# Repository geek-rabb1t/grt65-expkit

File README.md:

# GR-Trackpad65 experiment kit

The GR-Trackpad65 Experimental Kit is a kit for trying out the [GR-Trackpad65](https://github.com/geek-rabb1t/GR-Trackpad65).

It works as a macro pad with a trackpad for multi-touch support up to 4 fingers.

## Directory structure

This repository contains hardware design data only.

- pcb
    - PCB data designed by KiCAD.

## About Firmware

Vial firmware can be obtained from the following URL

- Vial
    - https://github.com/geek-rabb1t/vial-qmk/tree/gr_master/keyboards/geek_rabb1t/grt65_exp_kit

## Build Guide

Please read here.

- https://geek-rabb1t.github.io/grt65-expkit/build_guide

---
# GR-Trackpad65 実験キット

GR-Trackpad65 実験キットは [GR-Trackpad65](https://github.com/geek-rabb1t/GR-Trackpad65) を試すためのキットです。

4本指までのマルチタッチ対応のトラックパッド付きののマクロパッドとして機能します。

## ディレクトリ構造

このリポジトリにはハードウェアの設計データのみ格納しています。

- pcb
    - KiCADで設計したPCBデータ。

## ファームウェアについて

以下のURLにVial対応のファームウェアがあります。

- Vial
    - https://github.com/geek-rabb1t/vial-qmk/tree/gr_master/keyboards/geek_rabb1t/grt65_exp_kit

## 組み立て手順

こちらをご覧ください。

- https://geek-rabb1t.github.io/grt65-expkit/build_guide

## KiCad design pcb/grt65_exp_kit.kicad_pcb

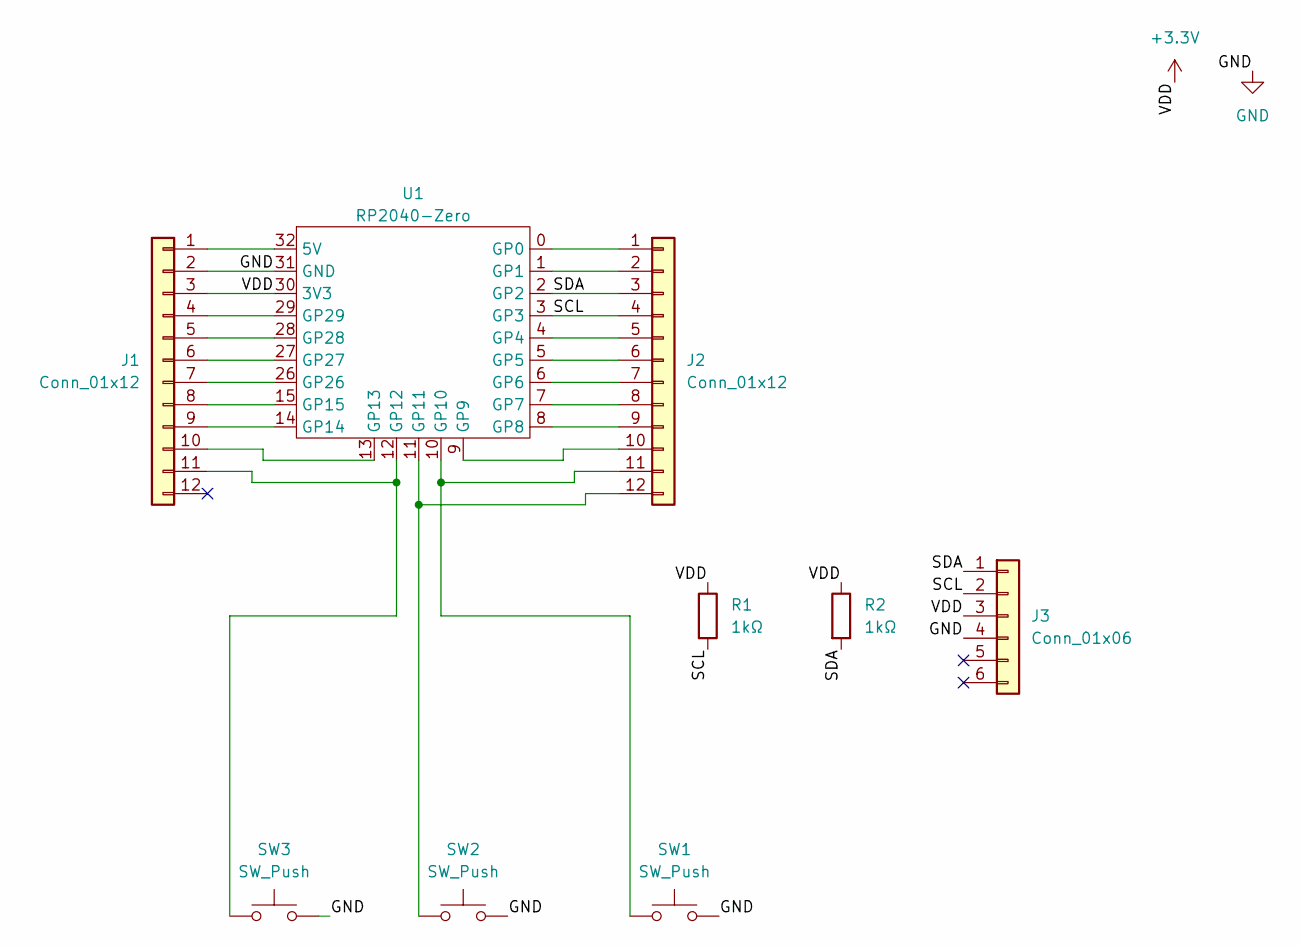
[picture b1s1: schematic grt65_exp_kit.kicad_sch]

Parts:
J1, J2: Conn_01x12; PinHeader_1x12_P2.54mm_Vertical
J3: Conn_01x06; Jushuo_AFC07-S06FCA-00_1x6-1MP_P0.50_Horizontal-JLC; LCSC Part # C11048
R1, R2: 1kΩ; R_0603_1608Metric
SW1, SW2, SW3: SW_Push; MX_Choc_solder
U1: RP2040-Zero

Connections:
+3.3V: J1.3, J3.3, R1.1, R2.1, U1.30 (3V3)
/SCL: J2.4, J3.2, R1.2, U1.3 (GP3)
/SDA: J2.3, J3.1, R2.2, U1.2 (GP2)
GND: J1.2, J3.4, SW1.2, SW2.2, SW3.2, U1.31 (GND)
unnamed: J1.1, U1.32 (5V)
unnamed: J1.4, U1.29 (GP29)
unnamed: J1.5, U1.28 (GP28)
unnamed: J1.6, U1.27 (GP27)
unnamed: J1.7, U1.26 (GP26)
unnamed: J1.8, U1.15 (GP15)
unnamed: J1.9, U1.14 (GP14)
unnamed: J1.10, U1.13 (GP13)
unnamed: J1.11, SW3.1, U1.12 (GP12)
unnamed: J2.1, U1.0 (GP0)
unnamed: J2.2, U1.1 (GP1)
unnamed: J2.5, U1.4 (GP4)
unnamed: J2.6, U1.5 (GP5)
unnamed: J2.7, U1.6 (GP6)
unnamed: J2.8, U1.7 (GP7)
unnamed: J2.9, U1.8 (GP8)
unnamed: J2.10, U1.9 (GP9)
unnamed: J2.11, SW1.1, U1.10 (GP10)
unnamed: J2.12, SW2.1, U1.11 (GP11)

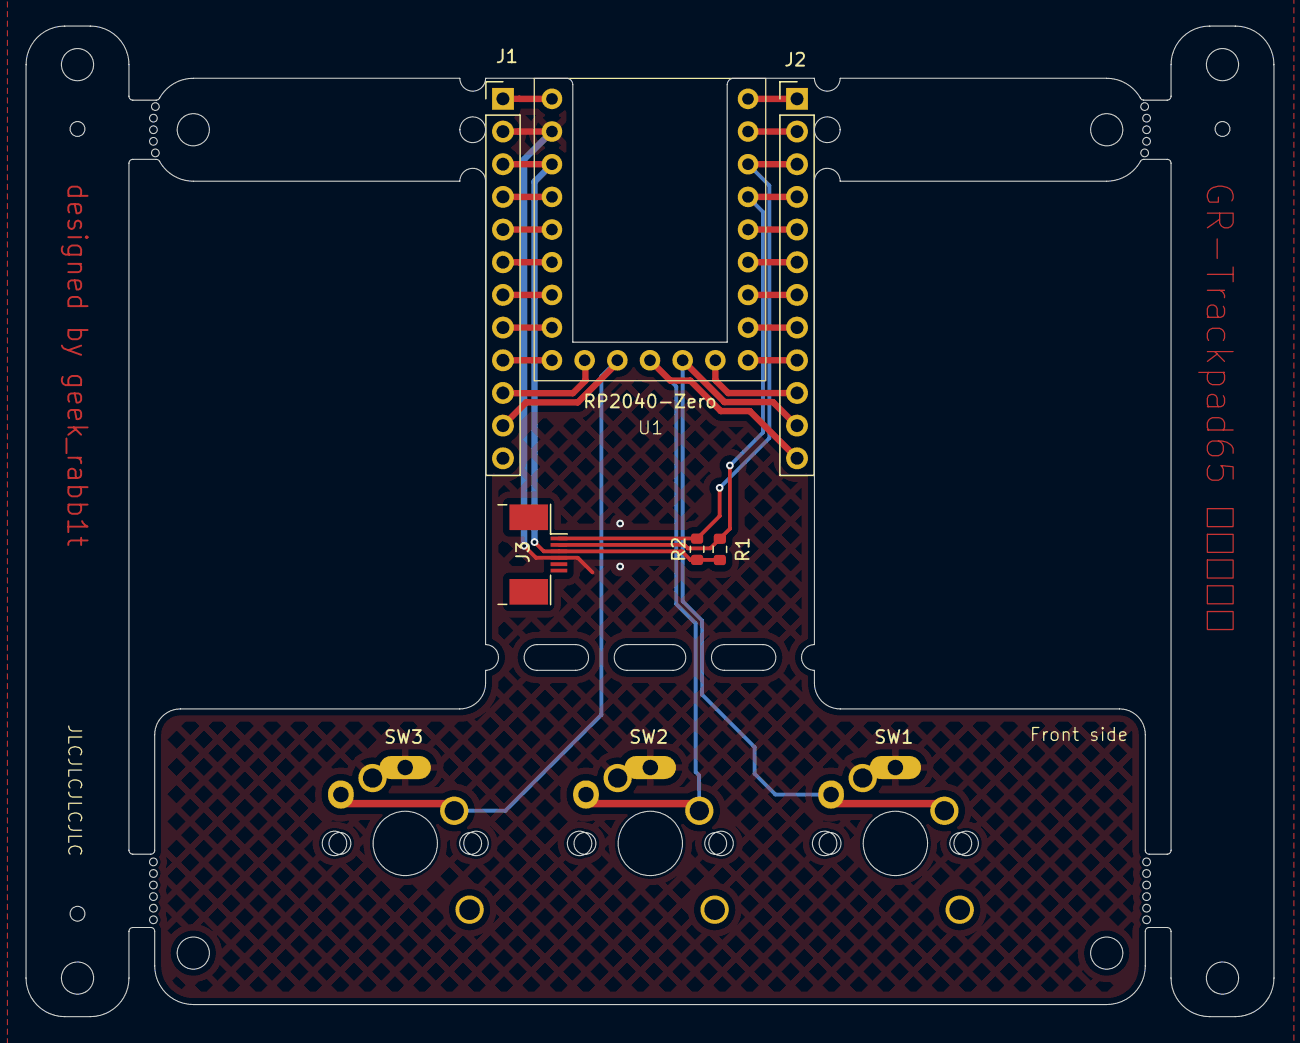
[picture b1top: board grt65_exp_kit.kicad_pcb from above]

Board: 2 copper layers, 97.0 x 77.0 mm, 9 parts (0 on the bottom side), 23 nets.

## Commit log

2025-03-12 add pcb desgin
2025-03-12 Update readme.
2025-06-26 Create geek_rabb1t_grt65_exp_kit_vial-v2-beta.uf2
    https://github.com/geek-rabb1t/vial-qmk/tree/8cee390adae20a445a61aa1a9dc2e1d9d3fc7249
2025-07-05 update firmware
